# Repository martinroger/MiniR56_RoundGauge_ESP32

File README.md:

An ESP32-based OBD Gauge for the R56 Mini Cooper

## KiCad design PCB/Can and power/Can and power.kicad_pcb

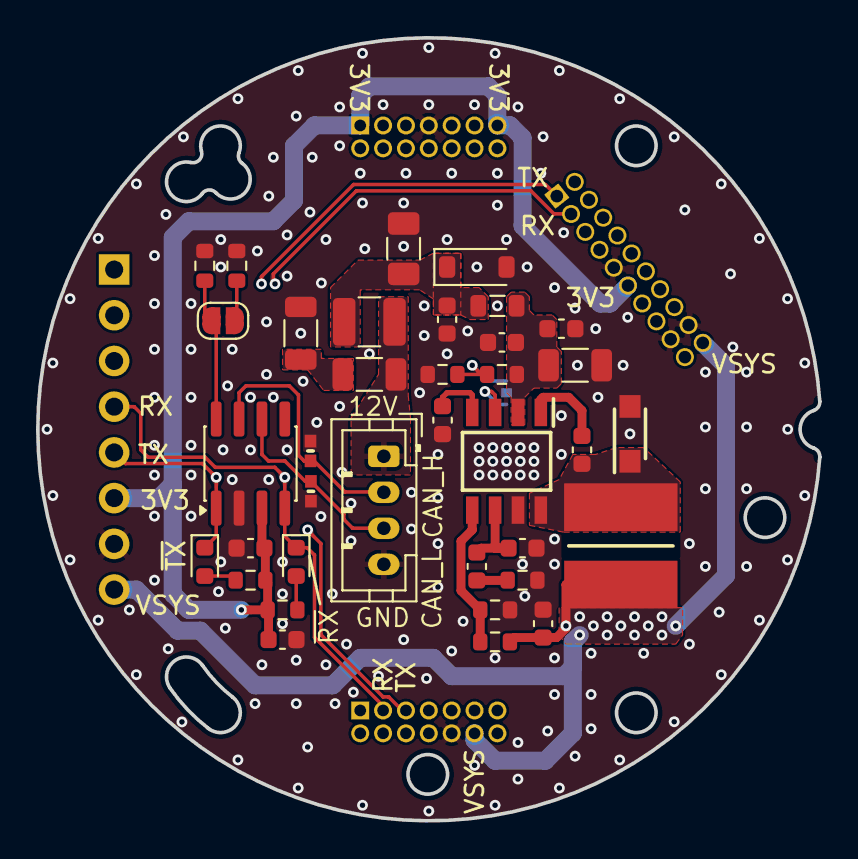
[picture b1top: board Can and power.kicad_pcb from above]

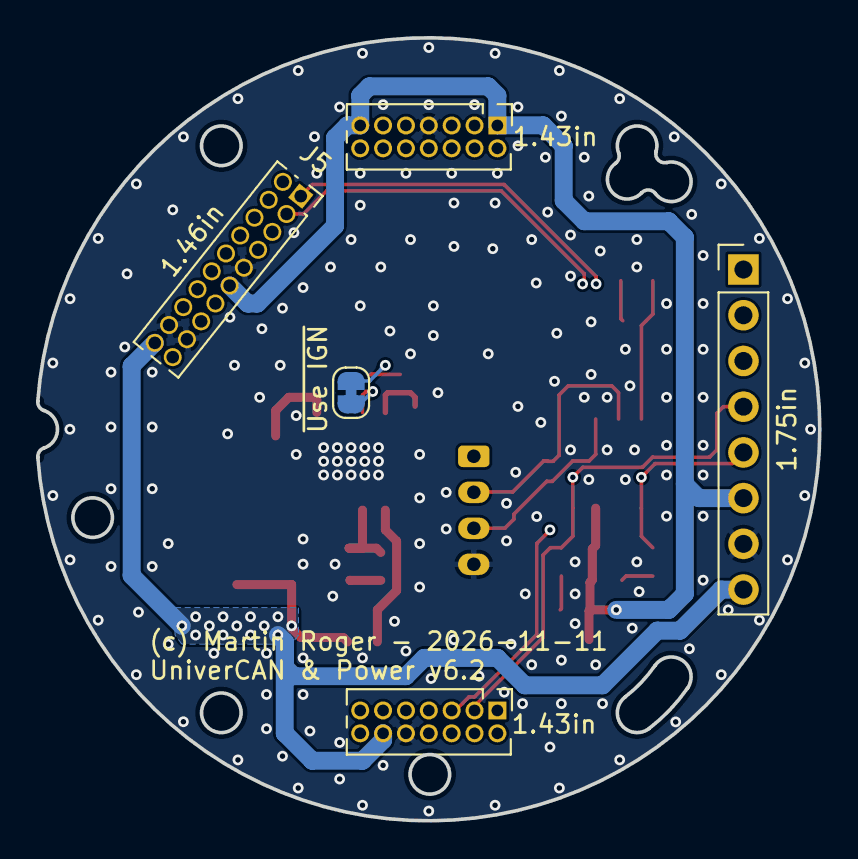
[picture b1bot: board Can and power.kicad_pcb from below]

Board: 4 copper layers, 43.4 x 43.5 mm, 41 parts (5 on the bottom side), 23 nets.

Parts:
C1, C2: 0.1uF 50V; C_0603_1608Metric
C3, C4, C10: 0.1uF; C_0603_1608Metric
C5: 1uF; C_0603_1608Metric
C6: 8200pF; C_0603_1608Metric
C7: 4700pF; C_0603_1608Metric
C8: 100pF; C_0603_1608Metric
C9: 10uF; C_1206_3216Metric
C11: 10uF; C_0603_1608Metric
C12: 0.1uF 50V; C_1206_3216Metric
D1, D2: PESD0402-140; DIONC1005X43N
D3: SS24FL; SODFL3617X108N
D4, D5: 2V - 20mA; LED_0603_1608Metric
D6: 18V; D_SOD-123
F1: 30V 500mA 2.5A-100ms; Fuse_1210_3225Metric
FB1: 120R@100MHz; L_0805_2012Metric
J3: HDR_143_1; PinHeader_2x07_P1.27mm_Vertical
J4: HDR_143_2; PinHeader_2x07_P1.27mm_Vertical
J5: SKT_146; PinSocket_2x10_P1.27mm_Vertical
J6: HDR_175; PinHeader_1x08_P2.54mm_Vertical
J7: Car connector; JST_PH_B4B-PH-K_1x04_P2.00mm_Vertical
JP1: High RS; SolderJumper-2_P1.3mm_Open_RoundedPad1.0x1.5mm
JP4: Use IGN; SolderJumper-2_P1.3mm_Bridged_RoundedPad1.0x1.5mm
L2: SRN6045TA-150M; INDC6060X450N
R1, R3: 1k; R_0603_1608Metric
R2, R9: 10k2; R_0603_1608Metric
R4: 12k7; R_0603_1608Metric
R8: 47k; R_0603_1608Metric
R10: 1k91; R_0603_1608Metric
R11: 100R; R_1206_3216Metric
RV1: B72520T0140K062; Fuse_1206_3216Metric
Ren1: 66k5; R_0603_1608Metric
Ren2: 7k5; R_0603_1608Metric
U1: SN65HVD230; SOIC-8_3.9x4.9mm_P1.27mm
U2: TPS54232DR; SOIC127P600X175-8N

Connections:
+3V3: C3.2, C4.1, J4.1, J4.13, J5.11, J6.6, R1.2, R3.1, U1.3 (VCC)
+12V: C12.2, F1.1, J7.1
/CAN_H: D1.1, J7.2, U1.7 (CANH)
/CAN_L: D2.1, J7.3, U1.6 (CANL)
GND: C1.1, C2.1, C3.1, C4.2, C5.2, C6.2, C8.2, C9.2, C11.2, D1.2, D2.2, D3.2, D6.2 (A), J3.10, J4.7, J5.9, J5.17, J5.18, J6.7, J7.4, R2.1, R4.1, R8.2, R10.1, R11.1, RV1.2, Ren2.1, U1.2 (GND), U2.7 (GND)
unnamed: C7.2, R4.2
unnamed: C12.1, R11.2
unnamed: D4.2 (A), R1.1
unnamed: D5.2 (A), R3.2
unnamed: C1.2, D6.1 (K), F1.2, FB1.1, RV1.1
unnamed: JP1.1 (A), R2.2
unnamed: JP1.2 (B), R8.1, U1.8 (Rs)
unnamed: JP4.1 (A), Ren1.1, Ren2.2
unnamed: JP4.2 (B), U2.3 (EN)
unnamed: C10.2, U2.1 (BOOT)
unnamed: C7.1, C8.1, U2.6 (COMP)
unnamed: C10.1, D3.1, L2.1, U2.8 (PH)
unnamed: C6.1, U2.4 (SS)
unnamed: C2.2, C5.1, C9.1, FB1.2, Ren1.2, U2.2 (VIN)
unnamed: R9.1, R10.2, U2.5 (VSENSE)
RX_CAN: D4.1 (K), J3.3, J5.3, J6.4, U1.4 (R)
TX_CAN: D5.1 (K), J3.5, J5.1, J6.5, U1.1 (D)
VSYS: C11.1, J3.12, J5.20, J6.8, L2.2, R9.2

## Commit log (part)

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2024-02-17 Working initial version
2024-02-17 Added more dependencies for accelerometer and touch
2024-02-17 Clean up
2024-02-17 Integrated QMI8658
2024-02-19 Added LVGL 9 binding
2024-02-19 LVGL Working, some buf messages
2024-02-20 Introducing SERIALDEBUG flag
2024-02-20 Displays acceleration
2024-02-20 Moving acceleration dot
2024-02-23 Kinda working version, no refresh
2024-02-23 Am an idiot
2024-03-04 Fonts for reference
2024-03-04 Base version screen
2024-03-04 Small corrections on font and display
2024-03-04 Annotations and start of cleanup
2024-03-04 Added filters Library reference
2024-03-04 Timer implementation
2024-03-04 Updating fake water
2024-03-10 Basic OBD functionality
2024-03-10 Floats are working
2024-03-25 PCB for shield
2024-03-26 Pre-traces
2024-03-27 First PCBWay quotation
2024-03-28 First purchase
2024-04-25 Change of transceiver
    For some reasons the TJA 1044 and 1049 get stuck in Standby mode all the time. Not sure why.
2024-04-25 LED resistor corrections
2024-04-26 Starting work for TWAI support
2024-04-26 Updated with TWAI implementation
2024-04-26 Lazy TWAI implementation
    Implemented TWAI of the ESP32S3 on pins 15 and 16. Still reversible to MCP2515 implementation but eventually that will get squashed out.
2024-04-26 Clean-up code and sch, PCB layout is a WIP
    Code limited to TWAI implementation
    Schematic updated with solder bridges
    PCB layout is a WIP
2024-04-26 Resistor correction
2024-04-27 New shield design
    New shield design. MCP2515 is gone and transceiver has moved to SN65HVD230
    Enable pin on the converter is used to cut off the uC when below 12V. Resistor values may have to change.
    No real protection on start up stage -> might need another layer for that
    Updated INO to reflect the changes in pinout
2024-05-21 Platform 6.7.0 compatibility trial
2024-05-21 Update platformio.ini
    Added release and corrected libraries
2024-05-21 Update main.cpp
    Cut out the CAN bit to focus on LVGL manipulation
2024-05-21 Update main.cpp
    Clock implementation works
    Trying to listen over serial now
2024-05-21 Update main.cpp
    Drawing Arc
    Trying to create an event callback between the text and the arc
2024-05-21 LV Event control of the arc via text value
2024-05-21 EVENT type adjustment
2024-05-21 KNOB adjustment
2024-05-21 Animation works !
2024-05-21 Faffing around with animation parameters
2024-05-22 Transition to EEZ
    Transition to EEZ with new screens. To be noted some aspects of the original build need to be modified a bit to make sure that the whole set of UI files can be generated directly from EEZ.
2024-05-23 Added action_go_to_next_screen to ui.c
2024-05-23 Minor sync
    EVENT_LONG_PRESSED instead of EVENT_PRESSED
2024-05-23 Semi colon correction
2024-05-23 Pre-Styles benchmark
2024-05-23 Styles benchmark
    No impact on RAM
    Minor on Flash (200 bytes)
2024-05-23 Adding arc refresh actions
2024-05-23 Adding functions and animations for arcs
2024-05-23 Value labels can be updated now
2024-05-23 setCanState functionality added
2024-05-23 First OBD test version
2024-06-04 No animate in background, placeholder vals
2024-06-04 Centered text
2024-06-07 Trying to introduce min/max gauges
2024-06-07 CAD reference update
2024-06-07 PoC : Min/Max gauges
2024-06-07 Coolant Scr functions simplification
2024-06-07 Min Maxes for the people !
2024-06-07 No floats, all mins maxs
2024-06-07 10% Animation lag for less frame splitting
2024-06-08 Added protection diode on voltage input
2024-06-08 Create LICENSE
2024-06-08 Added an image
2024-08-07 V4 PCB
    Ren1 and Ren2 values might not be discriminating enough
2024-08-08 Pending corrections on Ren1 and Ren2
    There is a discrepancy in the datasheet and the actual measured voltage hysteresis values. Increasing Ren1 and Ren2 to increase the trigger hysteresis.
2024-08-15 Update platformio.ini
    Locking Release version to latest library versions, aligning debug flag
2024-08-15 Ignition and Key Presence UI assets
    Implementation of booleans and UI labels for absence of Ignition, and absence of key.
2024-08-15 Ignition state and key state handling
    Wordy alerts on screen in case of loss of KL15 or key. No countdown to deep sleep or anything like that yet.
2024-08-15 Commenting
2024-08-15 Update platformio.ini
    Corrections for latest IDF
2024-08-24 Bugfixing
    - Re-export STEP of board with components in 3D
    - Boost gauge limits fixed #4
    - No OBD query if CAN down or key missing #2
    - Wait for successful first read to update screen #5
    - Mishmash delay added (to be removed)
    - Brightness increased to 200 from 128
2024-08-24 Update main.cpp
    - Check startup sequence gibberish shown on screen
2024-08-24 Hiding noise on startup, screen config is isolated
    - #6 is now fixed, solution is to start the screen dark and turn it on later in loop() via normal brightness control
    - Some hint about #7 that it may be a fade-in animation.
    - platformio.ini cleaned up
2024-08-24 Splash screen fixed
    Fixed #7 using differential load animation.
2024-08-24 Fix flickering issue
    Calling AnalogWrite every loop is unreasonable
2024-08-24 Minor cleanup
2024-08-27 Update main.cpp
    Default brightness update
2024-08-31 Prep classes
    KWP class for the main functions
    DID class for the basic DID information container
2024-09-06 Remanning
    Changing approach slightly
2024-09-07 Classes and structs
    - kwpFrame class for basic extended frame
    -kwp class for handling traffic and kwpFrames
    - DID struct to contain the DID definition metrics (could be a class but is a pain in the ass)
2024-09-07 Utils and base DIDs
2024-09-09 Update kwp.h
    Structure work
2024-09-09 Minor changes
    DIDs now store their value.
2024-09-09 KWP fleshing out
    Starting to write methods and sub-logic
2024-09-19 LVGL 9.2 EEz 0.16.1
    Updating to LVGL 9.2.0 and EEZ Studio 0.16.1 plus additional alignments of the ini file
2024-09-19 Update main.cpp
    Starter blending in
2024-10-11 Update platformio.ini
    ArduinoFilters update
2024-10-20 Resolutions
2024-10-20 Not working
2024-10-23 Rectifying board and background panel issues
2024-10-23 Start LVGL 9 port migration
2024-10-23 Continuing port corrections
2024-10-25 Further board and ESP_Panel conf
2024-10-25 Vars definition issue
2024-10-25 Removing vars.h
2024-10-25 Works without mins and maxs
2024-10-25 Touch zones update
2024-10-27 Timers removed
2024-10-27 Introducing vars.c
2024-10-27 MinsMaxs are back in the game
2024-10-27 Animation times and buffer adjustments
2024-10-27 External ANIMATE trigger and lv_timer_handler
2024-10-29 Functional viability
2024-10-29 Direct mode configuration
2024-10-31 Base functionality
2024-11-08 Copying files fro, KWPParser
2024-11-08 Basic KWP pipeline connection
2024-11-08 UI start of rework (non compiled)
2024-11-08 Sub-functions write-up
2024-11-08 Arc functions re-written
2024-11-08 Update screen functions
    Missing still the dataUpdateCB
2024-11-10 DataCB and corrections
2024-11-10 Corrections and base functionality
2024-11-10 Basic corrections, 0x130 basic implementation
2025-01-01 Update platformio.ini
    Moving to pioarduino 51.03.07
2025-03-11 Schematics and PCB update
2025-06-10 Mini VX Dash prototype
2025-06-10 Optimisation
2025-06-10 Buffer size optimisation
2025-06-10 Externalised LV conf
2025-06-10 Frankensteining
2025-06-11 Forgot the second buffer.
2025-06-11 Prep update
2025-06-11 Conversion v8 to v9, step 1
2025-06-11 Compiles, does not work
2025-06-11 Sort of working, TP reset not working, freezing
2025-06-11 Am an idiot
    Maybe mutex must be used all the way/...
2025-06-11 Works, poor performance
2025-06-11 TouchRead issues
2025-06-11 Update lv_conf.h
    Touch works
2025-06-11 Resolved collision between touchRead and mutex
2025-06-11 Pushing performance
2025-06-20 Experimenting with scales
2025-06-29 Works out of the box !
2025-06-29 Speed only
2025-06-29 Expander IO alignments
2025-07-02 Benchmark point vs ESP-IDF
2025-09-01 CanPower v5.1 preparation
2025-09-08 Universal cutout integration
2025-09-08 Partial schematic update
2025-09-08 Pre-PCB layout
2025-09-08 Need ERC corrections
2025-09-08 Projectification, correct footprints
2025-09-08 UniverCan v6.0
2025-09-10 Position refinements
2025-09-10 Cleanup
2025-09-16 Explicit callout to lib version, update to 1.0.4
    Reacting to an issue by @51hhh on the boilerplate repo. Colors are inverted, need to be moved as a PR for correction in the library. (TODO)
2025-09-22 v6.1 placeholder for bulk resistor and capacitor
2025-09-30 Digikey PN
2025-09-30 LCSC BOM finalisation
2025-10-01 Production order v6.1
2025-11-05 First production update
2025-11-30 Support DATA and Savvycan scripts
